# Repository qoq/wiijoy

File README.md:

# wiijoy
Adapter for connecting Wii Nunchuck or Wii Classic controller to Commodore, Atari, ZX Spectrum (Kempston) joystick port

The WiiJoy adapter supports both genuine and aftermarket Wii Nunchuck or Classic controllers.
WiiJoy adapter also supports "auto-fire" function (button C on Wii Nunchuck or B,Y,ZL,ZR on Wii Classic controller).

Beginning with version 1.0.6 (released Feb 05, 2023), the following features are supported:
- Accelerometer support for Nunchuck
- Up/Down direction swap
- Atari 2600 paddle-controller support 
- 2-button fire mode for Atari 7800 (BETA, not tested)

Nunchuck configuration:
- Holding Z while powering on enables 2-button fire mode
- Holding C while powering on enables accelerometer mode
- Holding DOWN while powering on swaps up and down direction
- Holding UP while powering on enables Atari 2600 paddle controller mode. In this mode, holding DOWN swaps L/R paddles

Wii Classic controller configuration:
- Select(-) button turns on 2-button fire mode
- Start(+)  button turns on up/down direction swap
- Home button resets all settings and restarts WiiJoy
- Holding UP on either stick while powering on (or while pressing Home) enables Atari 2600 paddle controller mode.

For Atari 7800 2-button mode:
Current PCB layout does not have traces connecting DB9 pins 5 and 9 to the MCU -- you must add two jumper wires (see schematic)
Turning 2-button support on is disables the auto-fire function

For Atari 2600 paddle controller mode:
Current PCB layout does not have circutry for this mode. You must add 4 resistors and 2 capacitors (see https://github.com/qoq/wiijoy/blob/main/pics/schematic_v2.png)

### Connecting Wii Nunchuck:
The Nunchuck's connector has three pins on one side and two pins on the other. Be sure to match them to 3 and 2-pin pads on WiiJoy PCB.

### Testing

- Plug WiiJoy into a joystick port. The LED should light up.
- Connect Wii Nunchuck/Classic  to the adapter. The LED should turn off (Controller detected). If the LED stays on, check Nunchuck connection.
- Press fire (Z). The LED should light up.
- Press (C) button. The LED should start blinking (this is the auto-fire function of the adapter).

Note that the metal "ears" of the pictured DB9 connector may need to be bent or cut to fit on some Atari machines. You can remove metal casing altogether, 
but you may need to glue two plastic parts of the connector together so they don't fall apart. Alternatively, you can use a different type of DB9 connector.

### Bill of materials

- [1] Resistor 330 Ohm 1/8w
- [3] Resistor 10 kOhm 1/8w
- [1] 5mm LED
- [1] 10 uF x 16v capacitor 
- [1] 3.3v voltage regulator -- STMicro L78L33ACZ or similar, TO92 package
- [1] DB9 female connector
- [1] Programmed PIC16Fxxx Microcontroller and PCB (eBay)

Additional parts required for 2600 paddle controler mode:
- [2] Resistor 330 Ohm 1/8w
- [2] Resistor 56 kOhm  (approximate value -- might neeed adjustments to calibrate/center paddle on screen)
- [2] 10 uF x 16v capacitor 

### The PCB & programmed MCU or complete DYI kit are available for purchasing on eBay

Have fun!

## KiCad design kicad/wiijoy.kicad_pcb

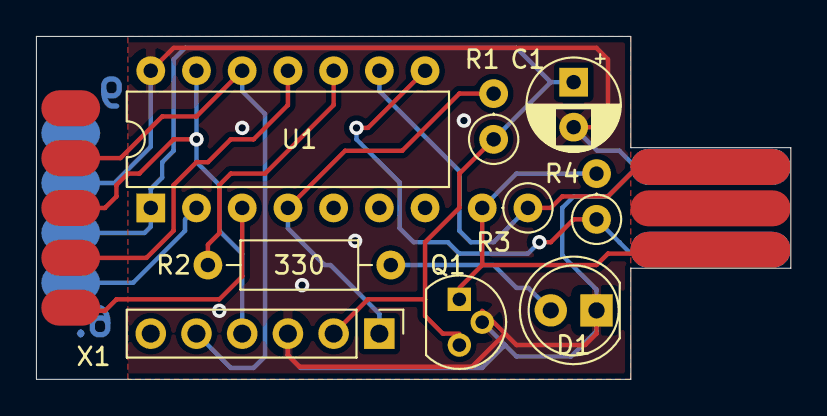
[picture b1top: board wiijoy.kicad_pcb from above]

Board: 2 copper layers, 41.9 x 19.1 mm, 9 parts (0 on the bottom side), 10 nets.

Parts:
C1: 10uF; CP_Radial_D5.0mm_P2.50mm
D1: LED; LED_D5.0mm
Q1: LP2950-3.3_TO92; TO-92
R1, R3, R4: 10k; R_Axial_DIN0207_L6.3mm_D2.5mm_P2.54mm_Vertical
R2: 330; R_Axial_DIN0207_L6.3mm_D2.5mm_P10.16mm_Horizontal
U1: PIC16F15223-I/P; DIP-14_W7.62mm
X1: ICSP; PinHeader_1x06_P2.54mm_Vertical

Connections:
+3V3: Q1.1, R3.2, R4.2
+5V: C1.1, Q1.3, R1.1, U1.1, X1.2
GND: C1.2, D1.1, Q1.2, U1.14, X1.3
unnamed: D1.2, R2.1
unnamed: R1.2, U1.4, X1.1
unnamed: R2.2, U1.10
unnamed: R3.1, U1.9
unnamed: R4.1, U1.8
unnamed: U1.12, X1.5
unnamed: U1.13, X1.4

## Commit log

2023-02-05 Accelerometer support, up/down swap support
2023-02-15 atari2600 mode added
